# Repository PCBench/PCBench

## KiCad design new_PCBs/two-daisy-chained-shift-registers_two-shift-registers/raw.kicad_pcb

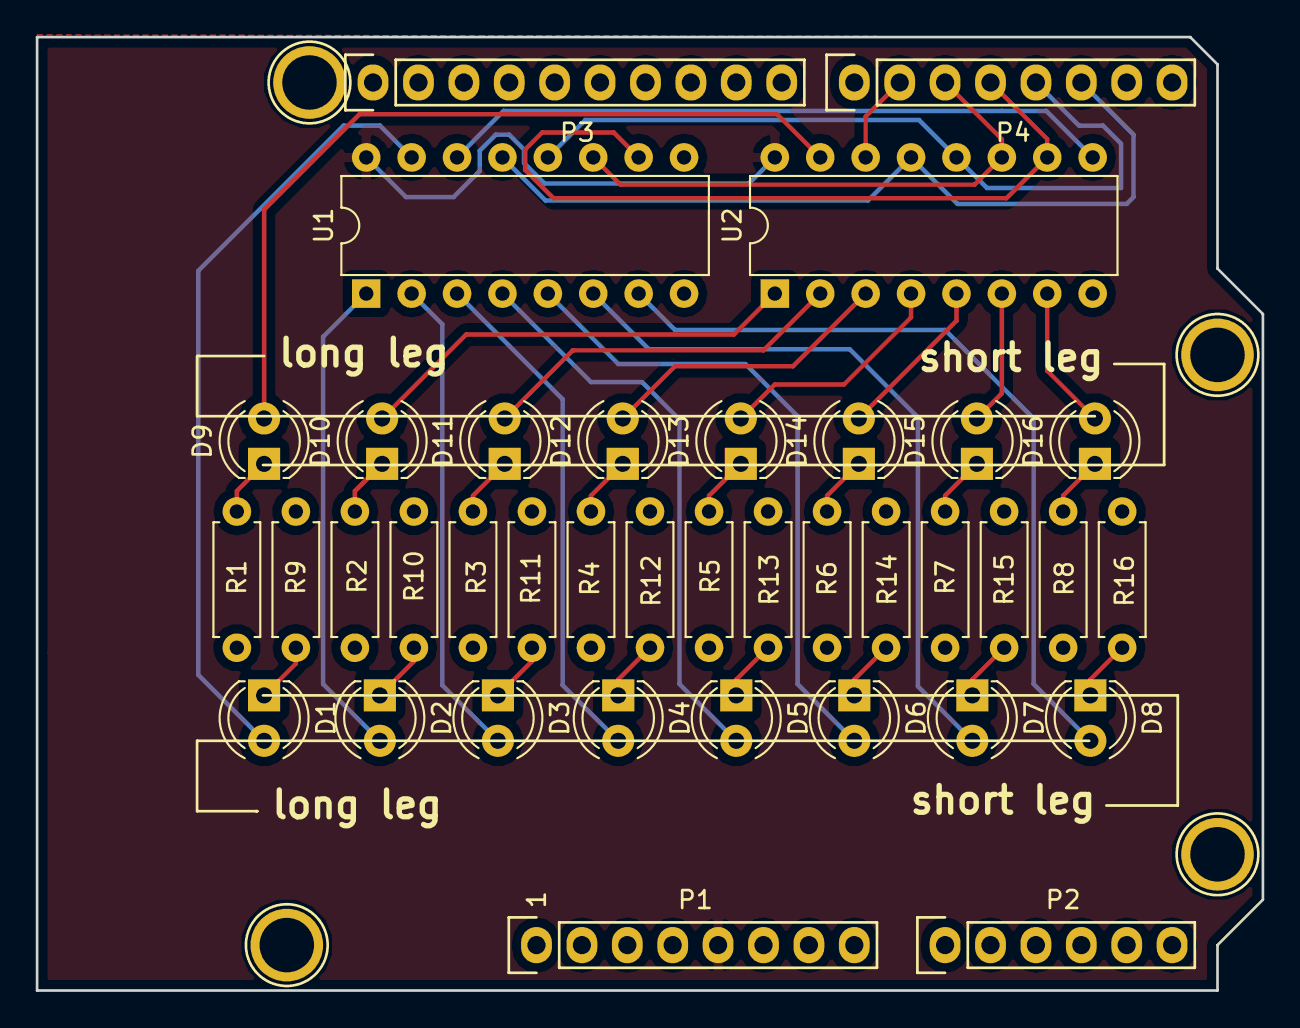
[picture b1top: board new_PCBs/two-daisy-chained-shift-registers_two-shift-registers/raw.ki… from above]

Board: 2 copper layers, 68.6 x 53.3 mm, 42 parts (0 on the bottom side), 40 nets.

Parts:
D1, D2, D3, D4, D5, D6, D7, D8, D9, D10, D11, D12, D13, D14, D15, D16: LED; LED_D4.0mm
P1: Power; Socket_Strip_Arduino_1x08
P2: Analog; Socket_Strip_Arduino_1x06
P3: Digital; Socket_Strip_Arduino_1x10
P4: Digital; Socket_Strip_Arduino_1x08
P5, P6, P7, P8: CONN_1; Arduino_1pin
R1, R2, R3, R4, R5, R6, R7, R8, R9, R10, R11, R12, R13, R14, R15, R16: 220; R_Axial_DIN0207_L6.3mm_D2.5mm_P7.62mm_Horizontal
U1, U2: 74HC595; DIP-16_W7.62mm

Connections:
+5V: P1.5, U1.16, U2.16
/2: P4.6, U1.13, U2.13
/3(**): P4.5, U1.12, U2.12
/4: P4.4, U1.10, U2.10
/5(**): P4.3, U1.11, U2.11
/6(**): P4.2, U2.14
GND: P1.6, P1.7, P3.4, R1.1, R2.1, R3.1, R4.1, R5.1, R6.1, R7.1, R8.1, R9.1, R10.1, R11.1, R12.1, R13.1, R14.1, R15.1, R16.1, U1.8, U2.8
unnamed: D9.1, R1.2
unnamed: D9.2, U2.15
unnamed: D10.1, R2.2
unnamed: D10.2, U2.1
unnamed: D11.1, R3.2
unnamed: D11.2, U2.2
unnamed: D12.1, R4.2
unnamed: D12.2, U2.3
unnamed: D13.1, R5.2
unnamed: D13.2, U2.4
unnamed: D14.1, R6.2
unnamed: D14.2, U2.5
unnamed: D15.1, R7.2
unnamed: D15.2, U2.6
unnamed: D16.1, R8.2
unnamed: D16.2, U2.7
unnamed: D1.1, R9.2
unnamed: D1.2, U1.15
unnamed: D2.1, R10.2
unnamed: D2.2, U1.1
unnamed: D3.1, R11.2
unnamed: D3.2, U1.2
unnamed: D4.1, R12.2
unnamed: D4.2, U1.3
unnamed: D5.1, R13.2
unnamed: D5.2, U1.4
unnamed: D6.1, R14.2
unnamed: D6.2, U1.5
unnamed: D7.1, R15.2
unnamed: D7.2, U1.6
unnamed: D8.1, R16.2
unnamed: D8.2, U1.7
unnamed: U1.14, U2.9

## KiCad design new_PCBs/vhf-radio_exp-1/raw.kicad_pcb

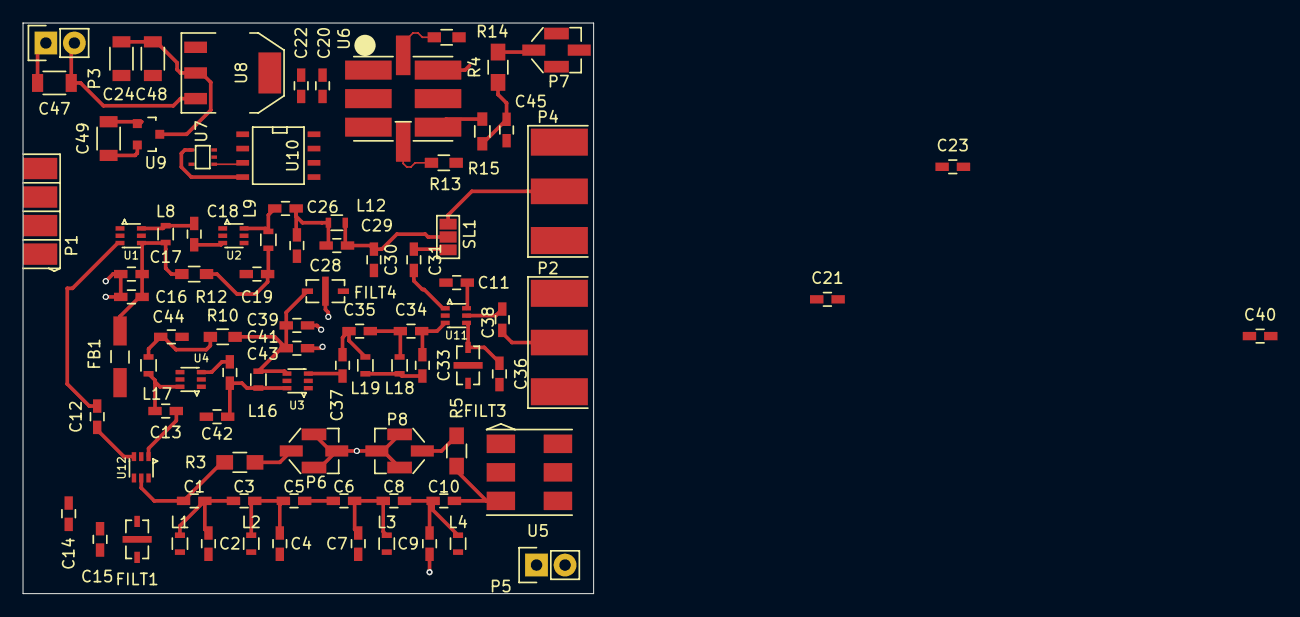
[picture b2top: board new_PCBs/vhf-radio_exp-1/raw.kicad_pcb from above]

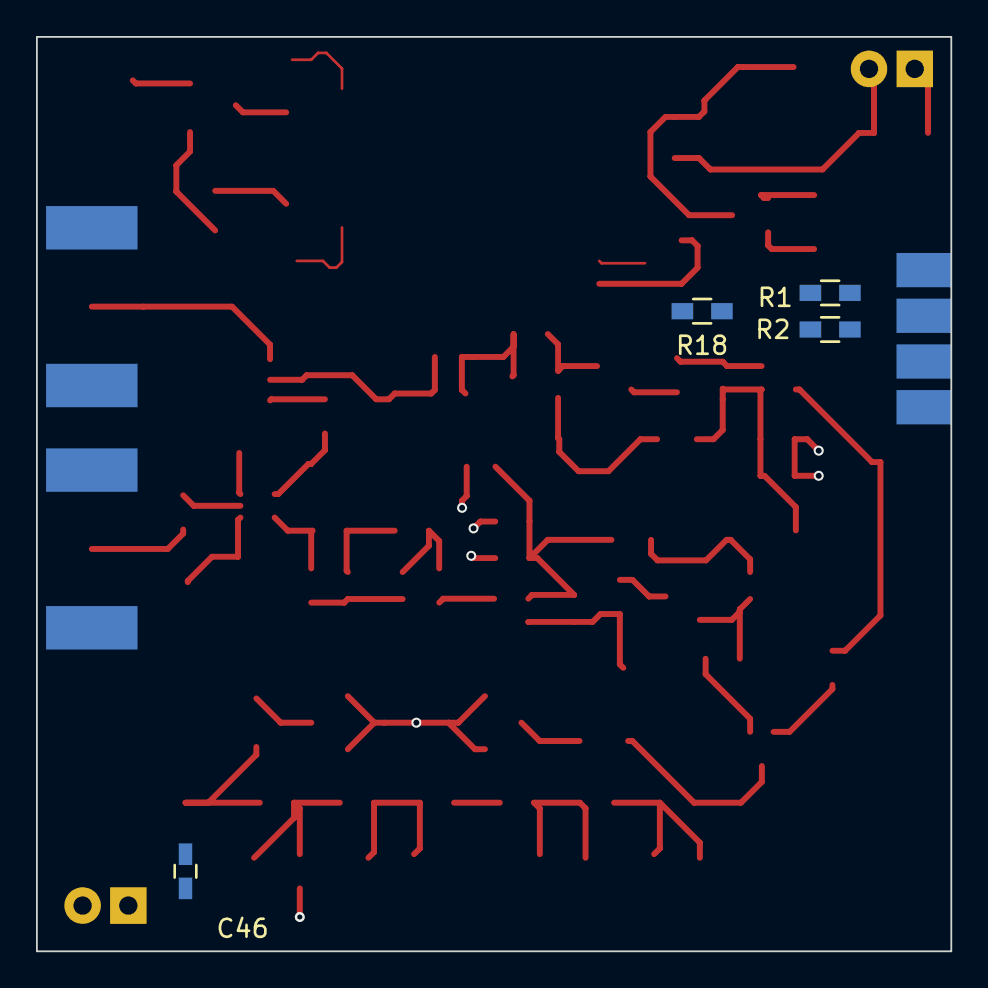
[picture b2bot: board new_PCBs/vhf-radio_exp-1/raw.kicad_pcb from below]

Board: 4 copper layers, 50.8 x 50.8 mm, 93 parts (4 on the bottom side), 53 nets.

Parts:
C1, C10: 2.7p; C_0603_HandSoldering
C2, C9, C29: 8.2p; C_0603_HandSoldering
C3, C5, C8: .5p; C_0603_HandSoldering
C4, C7, C34, C37: 12p; C_0603_HandSoldering
C6, C35: 1p; C_0603_HandSoldering
C11, C14, C15, C16, C17, C19, C20, C21, C22, C23, C36, C39, C41, C44: .01u; C_0603_HandSoldering
C12, C13, C18, C31, C38, C43, C45, C46: 470p; C_0603_HandSoldering
C24, C47, C48, C49: 22u; C_1206
C26, C28, C30: 15p; C_0603_HandSoldering
C33, C40: 47p; C_0603_HandSoldering
C42: 33p; C_0603_HandSoldering
FB1: FILTER; Choke_SMD_1206_Handsoldering
FILT1, FILT3, FILT4: MTFILT; FILTACH32T
L1, L4, L18, L19: 100n; R_0603
L2, L3: 91n; R_0603
L8, L9, L16, L17: .33u; R_0603
L12: 39n; R_0603
P1: CONN_8; 2x4_EDGE_.1
P2, P4: SMA; SMA_EMNT
P3, P5: CONN_2; Pin_Header_Straight_1x02
P6, P7, P8: U.FL; A-1JB
R1, R2, R18: 10K; R_0603_HandSoldering
R3, R4, R5: 0R; R_0805_HandSoldering
R10, R12: 30R; R_0603_HandSoldering
R13, R14: 1K; R_0603_HandSoldering
R15: 38R; R_0603_HandSoldering
SL1: SDRSEL; BSEL2
U1, U3: ABA-52563; SOT_363
U2, U4: AVT-50663; SOT_363
U5: ADE-1; PL-052
U6: Si570; SI570-HS
U7: 74AHC1G125; SOT-353
U8: NCP1117ST50T3G; SOT-223
U9: MCP1703T; SOT-23
U10: AP2152; SOIC-8-N
U11, U12: AS179-92LF; SOT_363

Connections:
+3.3V: C20.1, C22.1, C49.1, R13.2, R14.2, U6.2, U6.6, U9.2
/3V3: C21.1, P1.8, U7.5
/5V: C23.1, C24.1, C48.1, U8.2, U9.3, U10.2
/EN_RX: P1.6, R1.2, U7.1, U10.3
/EN_TX: P1.5, R2.2, U7.2
/IF: C46.1, P5.1
/LO: C45.1, U5.6
/SCL: P1.4, R13.1, U6.8
/SDA: P1.3, R14.1, U6.7
/TX_P: C29.2, C30.2, L12.2, SL1.1
/TX_SL: C31.1, SL1.3
/VIN: C47.1, P3.2, U8.3
/VRX: FILT1.3, FILT3.3, FILT4.3, U10.7
/VTX: C11.1, C14.1, FB1.2, U10.6, U11.6, U12.4
GND: C2.2, C4.2, C7.2, C9.2, C11.2, C14.2, C15.2, C16.2, C17.2, C19.2, C20.2, C21.2, C22.2, C23.2, C24.2, C28.1, C30.1, C33.2, C36.2, C39.2, C40.1, C41.2, C42.1, C44.2, C47.2, C48.2, C49.2, FILT1.2, FILT3.2, FILT4.2, L1.2, L2.2, L3.2, L4.2, L18.2, L19.2, P1.7, P2.2, P3.1, P4.2, P5.2, P6.2, P7.2, P8.2, R1.1, R2.1, R18.1, U1.1, U1.2, U1.5, U2.1, U2.2, U2.4, U2.5, U3.1, U3.2, U3.5, U4.1, U4.2, U4.4, U4.5, U5.1, U5.4, U5.5, U6.3, U7.3, U8.1, U9.1, U10.1, U11.2, U12.2
unnamed: C1.1, C2.1, C3.2, L1.1
unnamed: C1.2, R3.2, U12.5
unnamed: C3.1, C4.1, C5.2, L2.1
unnamed: C5.1, C6.2
unnamed: C6.1, C7.1, C8.2, L3.1
unnamed: C10.1, R5.2, U5.3
unnamed: C8.1, C9.1, C10.2, L4.1
unnamed: C12.1, U12.3
unnamed: C12.2, U1.3
unnamed: C13.1, U12.1
unnamed: C13.2, L17.2, U4.6
unnamed: C15.1, FILT1.1, U12.6
unnamed: C16.1, C17.1, FB1.1, L8.1, R12.2, U1.4
unnamed: C18.1, U2.3
unnamed: C18.2, L8.2, U1.6
unnamed: C19.1, L9.1, R12.1
unnamed: C26.1, C28.2, C29.1, L12.1
unnamed: C26.2, L9.2, U2.6
unnamed: C31.2, U11.1
unnamed: C33.1, C34.2, U11.3
unnamed: C34.1, C35.2, L18.1
unnamed: C35.1, C37.2, L19.1
unnamed: C36.1, FILT3.1, U11.4
unnamed: C37.1, C40.2, U3.3
unnamed: C38.1, P2.1
unnamed: C38.2, U11.5
unnamed: C39.1, C41.1, FILT4.1, L16.1, R10.2, U3.4
unnamed: C42.2, C43.2, L16.2, U3.6
unnamed: C43.1, U4.3
unnamed: C44.1, L17.1, R10.1
unnamed: C45.2, R4.1, R15.1
unnamed: C46.2, U5.2
unnamed: P4.1, SL1.2
unnamed: P6.1, R3.1
unnamed: P7.1, R4.2
unnamed: P8.1, R5.1
unnamed: R15.2, U6.4
unnamed: R18.2, U7.4, U10.4

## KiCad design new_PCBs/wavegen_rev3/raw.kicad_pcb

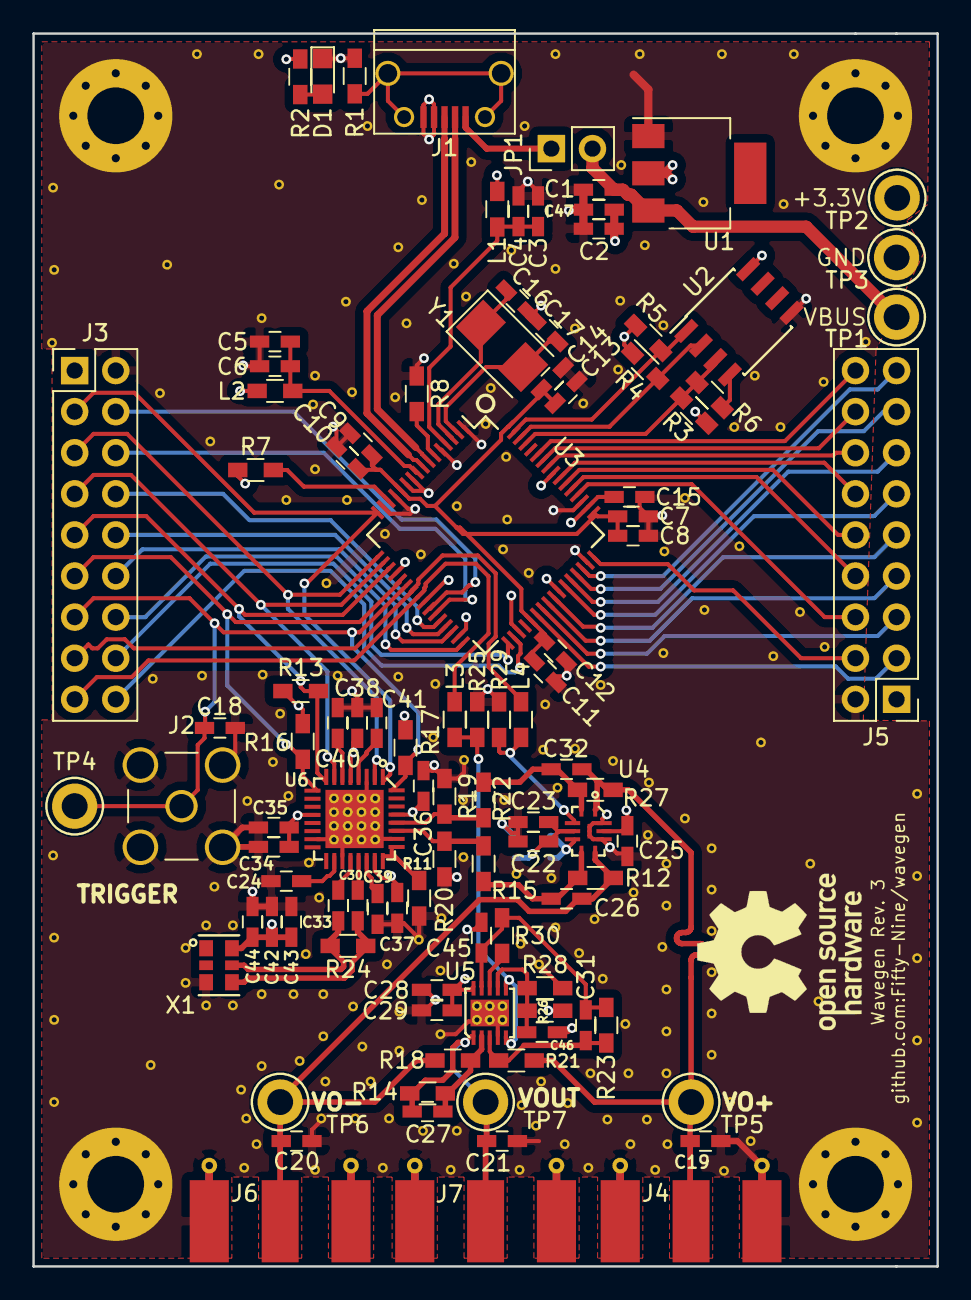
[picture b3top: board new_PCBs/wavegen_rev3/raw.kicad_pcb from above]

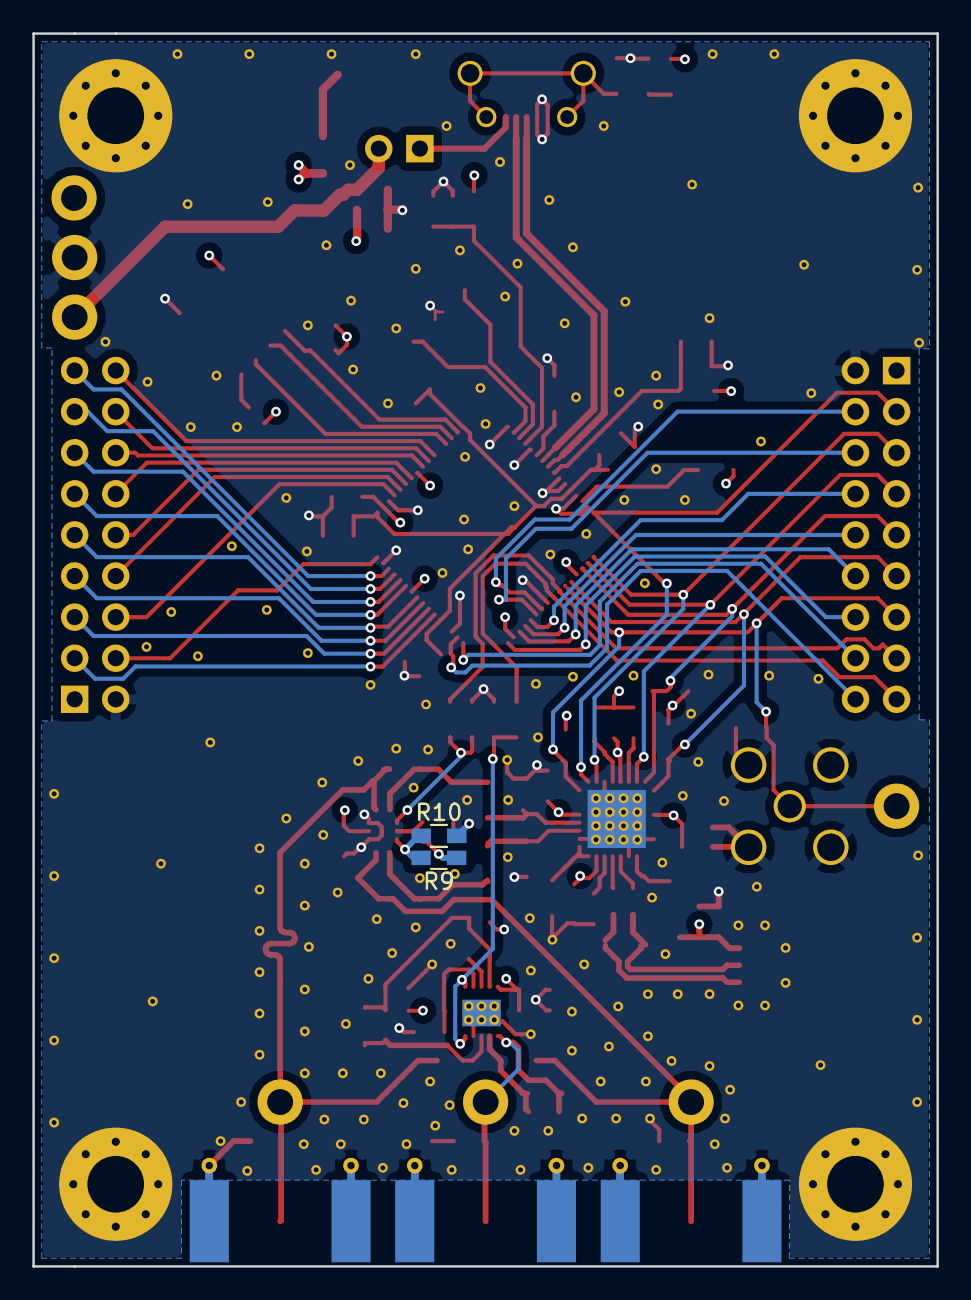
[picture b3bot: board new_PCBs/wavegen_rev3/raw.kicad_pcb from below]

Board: 4 copper layers, 55.9 x 76.2 mm, 105 parts (2 on the bottom side), 75 nets.

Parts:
 C19: DNP; C_0603_HandSoldering
C1, C4, C6, C8, C9, C10, C11, C12, C13, C14, C15, C23, C24, C25, C28, C30, C33, C35, C36, C37, C38, C39, C40, C41, C44, C47: 100n; C_0603_HandSoldering
C2, C22, C29, C34, C42: 10u; C_0603_HandSoldering
C3, C5, C45: 4.7u; C_0603_HandSoldering
C7: 3.3u; C_0603_HandSoldering
C16, C17: 27p; C_0603_HandSoldering
C18, C20, C21: DNP; C_0603_HandSoldering
C26, C32: 0.8p; C_0603_HandSoldering
C27, C31: 2.8p; C_0603_HandSoldering
C43, C46: 1u; C_0603_HandSoldering
D1: Green; LED_0805
J1: USB_B; USB_Micro-B-circular
J2: SMA; SMA_THT_Jack_Straight
J3, J5: CONN_02X09; Pin_Header_Straight_2x09_Pitch2.54mm
J4, J6, J7: SMA; Molex_SMA_Jack_Edge_Mount
JP1: USB_PWR; Pin_Header_Straight_1x02_Pitch2.54mm
L1, L2, L3, L4: 800m; L_0603_HandSoldering
R1, R9, R10: DNP; R_0603_HandSoldering
R2: 500; R_0603_HandSoldering
R3, R4, R5: 10k; R_0603_HandSoldering
R6: 2.2k; R_0603_HandSoldering
R7, R13, R16, R17, R25, R29: 4.7k; R_0603_HandSoldering
R8: 12k; R_0603_HandSoldering
R11: 8.25k; R_0603_HandSoldering
R12, R27: 510; R_0603_HandSoldering
R14, R23: 1.5k; R_0603_HandSoldering
R15, R19, R20, R22, R24: 100; R_0603_HandSoldering
R18, R21: 1k; R_0603_HandSoldering
R26, R28: 36k; R_0603_HandSoldering
R30: 18k; R_0603_HandSoldering
TP1: VBUS; Test_Point_Keystone_5005-5009_Compact
TP2: +3.3V; Test_Point_Keystone_5005-5009_Compact
TP3: GND; Test_Point_Keystone_5005-5009_Compact
TP4: TRIGGER; Test_Point_Keystone_5005-5009_Compact
TP5: VOUT+; Test_Point_Keystone_5005-5009_Compact
TP6: VOUT-; Test_Point_Keystone_5005-5009_Compact
TP7: VOUT; Test_Point_Keystone_5005-5009_Compact
U1: LD1117S33TR; SOT-223
U2: 93LCxxB; SOIC-8_3.9x4.9mm_Pitch1.27mm
U3: FT2232H; LQFP-64_10x10mm_Pitch0.5mm
U4: LTC6409; LTC6409-UDB
U5: LTC6269; LTC6269-10DFN
U6: AD9102; AD9102-10LFCSP
X1: DSC1123; 3225XO
Y1: 12MHz; Crystal_SMD_5032-2pin_5.0x3.2mm

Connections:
+3V3: C2.1, C15.1, C22.1, C23.1, C25.1, C28.1, C29.1, C34.2, C35.2, C36.2, C37.1, C38.1, C42.1, C43.1, C44.1, C47.1, J3.1, J5.1, L1.1, L2.1, R2.1, R3.1, R4.1, R5.1, R7.1, R9.1, R13.1, R16.1, R17.1, R26.1, TP2.1, U1.2, U2.8, U3.20, U3.31, U3.42, U3.50, U3.56, U4.4, U4.9, U5.10, U6.5, U6.12, U6.23, U6.29, X1.6
/Analog/+1.65V: C31.1, C45.1, R23.2, R30.2, U5.9
/Connectors/ACBUS0: J3.4, U3.26
/Connectors/ACBUS1: J3.6, U3.27
/Connectors/ACBUS2: J3.8, U3.28
/Connectors/ACBUS3: J3.10, U3.29
/Connectors/ACBUS4: J3.12, U3.30
/Connectors/ACBUS5: J3.14, U3.32
/Connectors/ACBUS6: J3.16, U3.33
/Connectors/ACBUS7: J3.18, U3.34
/Connectors/BCBUS0: J5.4, U3.48
/Connectors/BCBUS1: J5.6, U3.52
/Connectors/BCBUS2: J5.8, U3.53
/Connectors/BCBUS3: J5.10, U3.54
/Connectors/BCBUS4: J5.12, U3.55
/Connectors/BCBUS5: J5.14, U3.57
/Connectors/BCBUS6: J5.16, U3.58
/Connectors/BCBUS7: J5.18, U3.59
/Connectors/BDBUS0: J5.3, U3.38
/Connectors/BDBUS1: J5.5, U3.39
/Connectors/BDBUS2: J5.7, U3.40
/Connectors/BDBUS3: J5.9, U3.41
/Connectors/BDBUS4: J5.11, U3.43
/Connectors/BDBUS5: J5.13, U3.44
/Connectors/BDBUS6: J5.15, U3.45
/Connectors/BDBUS7: J5.17, U3.46
/FTDI/REF: R8.2, U3.6
/FTDI/VREGOUT: C7.1, C8.1, C9.1, C10.1, C11.1, C12.1, C13.1, C14.1, U3.12, U3.37, U3.49, U3.64
/FTDI/nRESET: R7.2, U3.14
AMP0_EN: J3.15, L4.1, U3.23
AMP1_EN: J3.17, L3.2, U3.24
DCLK+: C30.2, R24.1, X1.4
DCLK-: C33.2, R24.2, X1.5
FTEECLK: R4.2, U2.2, U3.62
FTEECS: R5.2, U2.1, U3.63
FTEEDATA: R3.2, R6.1, U2.3, U3.61
FTOSC+: C16.1, U3.3, Y1.1
FTOSC-: C17.1, U3.2, Y1.2
FTVPHY: C3.1, C4.1, L1.2, U3.4
FTVPLL: C5.1, C6.1, L2.2, U3.9
GNDA: C19.1, C1.2, C2.2, C3.2, C4.2, C5.2, C6.2, C7.2, C8.2, C9.2, C10.2, C11.2, C12.2, C13.2, C14.2, C15.2, C16.2, C17.2, C18.1, C20.1, C21.1, C22.2, C23.2, C24.1, C25.2, C28.2, C29.2, C34.1, C35.1, C36.1, C37.2, C38.2, C39.2, C40.2, C41.2, C42.2, C43.2, C44.2, C45.2, C46.2, C47.2, D1.1, J1.4, J2.2, J3.2, J4.2, J5.2, J6.2, J7.2, R1.1, R8.1, R10.2, R11.1, R19.1, R20.1, R25.2, R28.2, R29.2, TP3.1, U1.1, U2.5, U3.1, U3.5, U3.10, U3.11, U3.13, U3.15, U3.25, U3.35, U3.47, U3.51, U4.8, U4.10, U4.11, U5.4, U5.11, U6.3, U6.15, U6.19, U6.26, U6.EP, X1.3
unnamed: C1.1, JP1.2, TP1.1, U1.3
unnamed: C24.2, U6.18
unnamed: C26.2, R12.1, R15.2, U4.6
unnamed: C27.1, R14.2, R18.2, U5.2
unnamed: C30.1, U6.21
unnamed: C31.2, R21.2, R23.1, U5.3
unnamed: C32.2, R22.2, R27.1, U4.2
unnamed: C33.1, U6.20
unnamed: C39.1, U6.22
unnamed: C40.1, U6.6
unnamed: C41.1, U6.4
unnamed: C46.1, R26.2, R28.1, U5.7
unnamed: D1.2, R2.2
unnamed: J1.1, JP1.1
unnamed: J1.5, R1.2
unnamed: L3.1, R25.1, U5.5, U5.6
unnamed: L4.2, R29.1, U4.3
unnamed: R6.2, U2.4
unnamed: R11.2, U6.24, U6.25
unnamed: R15.1, R20.2, U6.27
unnamed: R19.2, R22.1, U6.28
unnamed: R30.1, U5.8
RESET: J3.11, R16.2, U3.21, U6.9
SPI_CLK: J3.3, U3.16, U6.1
SPI_CS: J3.9, R13.2, U3.19, U6.8
SPI_DI: J3.7, U3.18, U6.7
SPI_DO: J3.5, U3.17, U6.2
TRIGGER: C18.2, J2.1, J3.13, R17.2, TP4.1, U3.22, U6.32
USB_D+: J1.3, U3.8
USB_D-: J1.2, U3.7
VOCM: R9.2, R10.1, U4.5
VOUT: C21.2, C27.2, J7.1, R14.1, TP7.1, U5.1
VOUT+: C19.2, C32.1, J4.1, R21.1, R27.2, TP5.1, U4.1
VOUT-: C20.2, C26.1, J6.1, R12.2, R18.1, TP6.1, U4.7

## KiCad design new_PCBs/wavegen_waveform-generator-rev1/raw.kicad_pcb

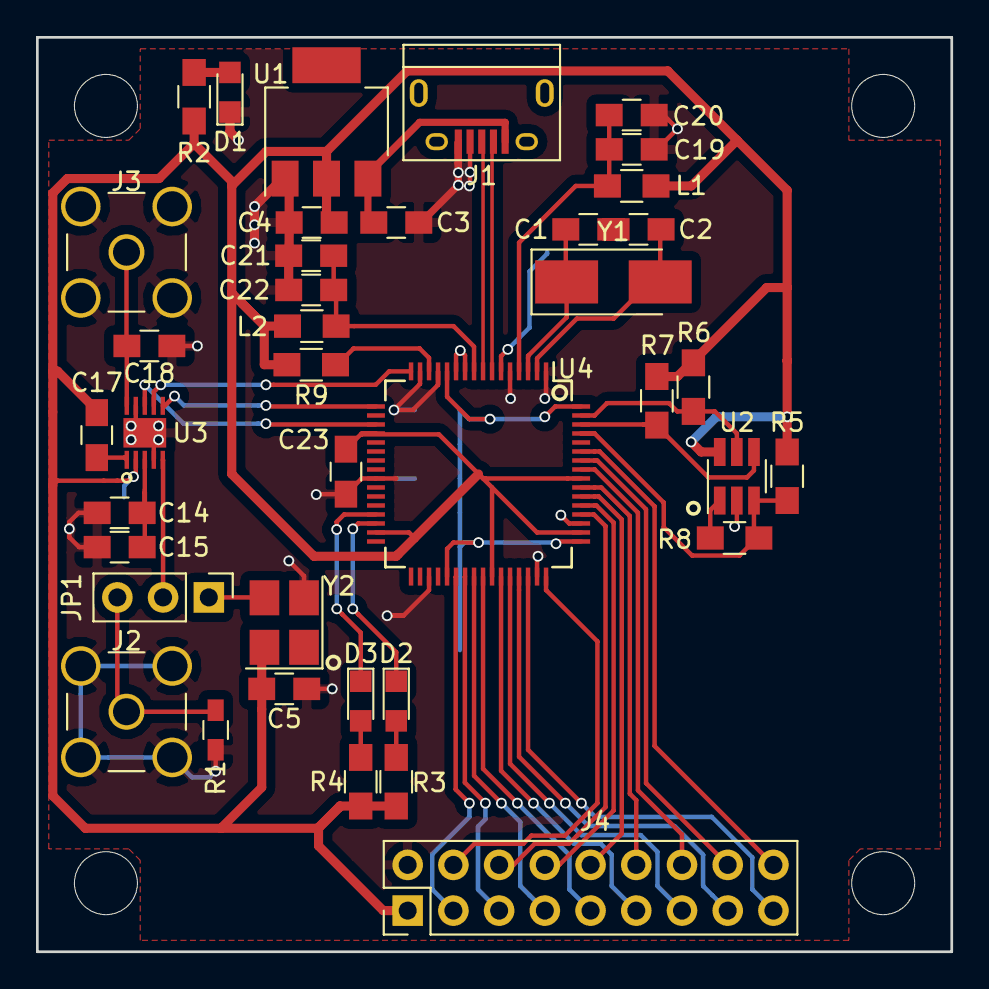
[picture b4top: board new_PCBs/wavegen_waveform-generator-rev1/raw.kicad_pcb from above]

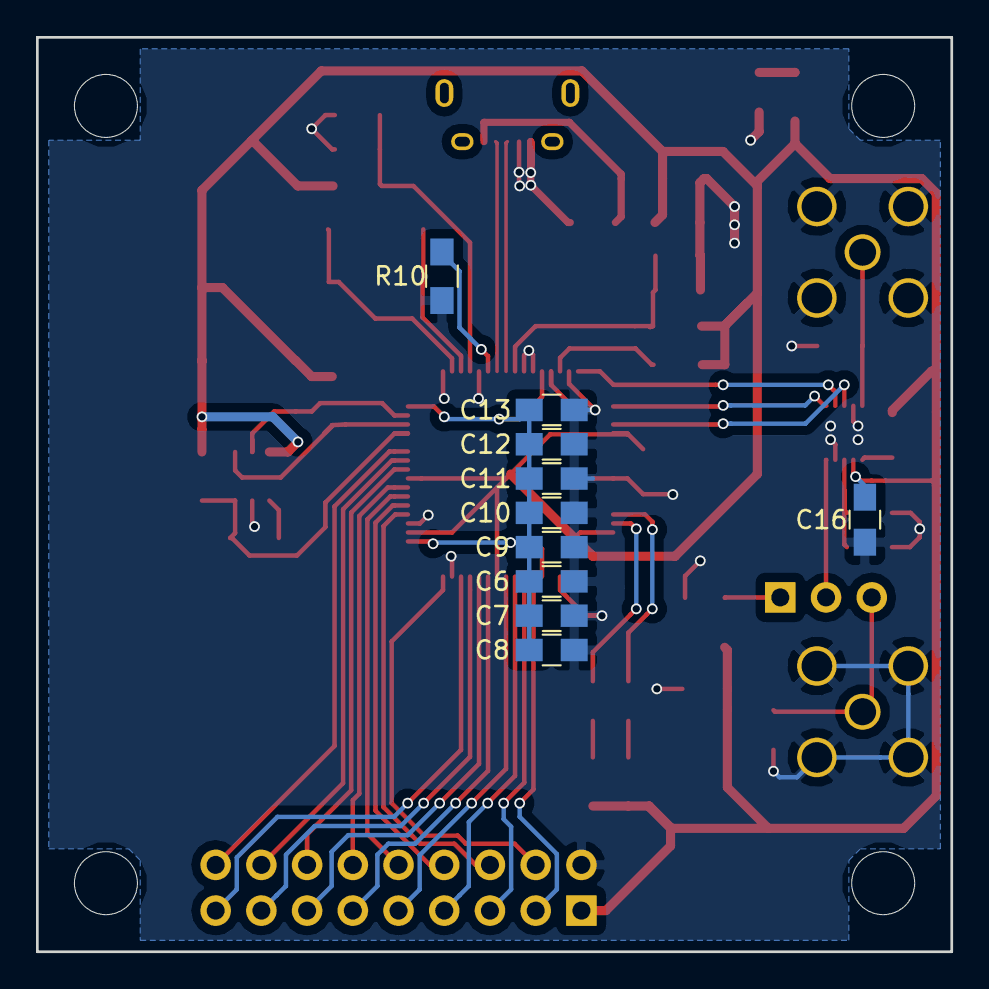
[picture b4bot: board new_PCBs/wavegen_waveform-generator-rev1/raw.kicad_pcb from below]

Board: 2 copper layers, 50.8 x 50.8 mm, 49 parts (10 on the bottom side), 47 nets.

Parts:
C1, C2: 27p; C_0805_HandSoldering
C3, C5, C7, C8, C9, C10, C11, C12, C13, C14, C16, C18, C20, C22, C23: 100n; C_0805_HandSoldering
C4, C15: 10u; C_0805_HandSoldering
C6: 3.3u; C_0805_HandSoldering
C17: 10n; C_0805_HandSoldering
C19, C21: 4.7u; C_0805_HandSoldering
D1, D2, D3: LED_Small; LED_0805
J1: USB_B; USB_Micro-B
J2: EXT_CLK; SMA_THT_Jack_Straight
J3: VOUT; SMA_THT_Jack_Straight
J4: CONN_02X09; Pin_Header_Straight_2x09_Pitch2.54mm
JP1: CLK_SELECT; Pin_Header_Straight_1x03_Pitch2.54mm
L1, L2: 800m; L_0805_HandSoldering
R1: 50; R_0603_HandSoldering
R2, R3, R4: 470; R_0805_HandSoldering
R5, R6, R7: 10k; R_0805_HandSoldering
R8: 2.2k; R_0805_HandSoldering
R9: 1k; R_0805_HandSoldering
R10: 12k; R_0805_HandSoldering
U1: LD1117S33TR; SOT-223
U2: 93LC46BT; SOT-23-6_Handsoldering
U3: AD9837
U4: FT2232H; LQFP-64_10x10mm_Pitch0.5mm
Y1: 12MHz; Crystal_SMD_5032-2pin_5.0x3.2mm_HandSoldering
Y2: OXETGCJANF; Oscillator_SMD_Abracon_ASE-4pin_3.2x2.5mm_HandSoldering

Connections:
+3V3: C4.1, C5.1, C16.1, C17.1, C23.1, J4.1, L1.1, L2.1, R2.2, R3.2, R4.2, R5.1, R6.1, R7.1, R9.2, U1.2, U2.6, U3.2, U4.20, U4.31, U4.42, U4.50, U4.56, Y2.4
DAC_CLK: JP1.2, U3.5
EECLK: R7.2, U2.4, U4.62
EECS: R6.2, U2.5, U4.63
EEDATA: R5.2, R8.1, U2.3, U4.61
FTOSCI: C2.1, U4.2, Y1.2
FTOSCO: C1.1, U4.3, Y1.1
FTRXLED: D3.1, U4.29
FTTXLED: D2.1, U4.30
FTVPHY: C19.1, C20.1, L1.2, U4.4
FTVPLL: C21.1, C22.1, L2.2, U4.9
GNDA: C3.2, C4.2, C5.2, C6.2, C7.2, C8.2, C9.2, C10.2, C11.2, C12.2, C13.2, C14.2, C15.2, C16.2, C18.2, C19.2, C20.2, C21.2, C22.2, C23.2, D1.1, J1.4, J1.5, J2.2, J3.2, J4.2, R1.2, R10.2, U1.1, U2.2, U3.4, U3.9, U3.11, U4.1, U4.5, U4.10, U4.11, U4.13, U4.15, U4.25, U4.35, U4.47, U4.51, Y2.2
unnamed: C1.2, C2.2
unnamed: C3.1, J1.1, U1.3
unnamed: C6.1, C7.1, C8.1, C9.1, C10.1, C11.1, C12.1, C13.1, U4.12, U4.37, U4.49, U4.64
unnamed: C14.1, C15.1, U3.3
unnamed: C17.2, U3.1
unnamed: C18.1, J3.1, U3.10
unnamed: D1.2, R2.1
unnamed: D2.2, R3.1
unnamed: D3.2, R4.1
unnamed: J2.1, JP1.3, R1.1
unnamed: J4.3, U4.38
unnamed: J4.4, U4.48
unnamed: J4.5, U4.39
unnamed: J4.6, U4.52
unnamed: J4.7, U4.40
unnamed: J4.8, U4.53
unnamed: J4.9, U4.41
unnamed: J4.10, U4.54
unnamed: J4.11, U4.43
unnamed: J4.12, U4.55
unnamed: J4.13, U4.44
unnamed: J4.14, U4.57
unnamed: J4.15, U4.45
unnamed: J4.16, U4.58
unnamed: J4.17, U4.46
unnamed: J4.18, U4.59
unnamed: JP1.1, Y2.3
unnamed: R8.2, U2.1
unnamed: R9.1, U4.14
unnamed: R10.1, U4.6
unnamed: U3.6, U4.17
unnamed: U3.7, U4.16
unnamed: U3.8, U4.19
USB_D+: J1.3, U4.8
USB_D-: J1.2, U4.7
